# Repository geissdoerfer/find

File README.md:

# Efficient neighbor discovery and synchronization in battery-free wireless networks with FIND and FLYNC

This repository hosts the artifacts accompanying our NSDI 2021 paper, which introduces FIND and FLYNC.
FIND is the first neighbor discovery protocol for battery-free networks; it uses randomized waiting to minimize discovery latency in the face of intermittency.
FLYNC synchronizes indoor light harvesting devices to the powerline-induced brightness variations of state-of-the-art lamps; it further speeds up discovery when used in tandem with FIND.

In addition to the Python implementation of the analytical FIND model, we provide the hardware design of the prototype battery-free node and the source code of the firmware we used to evaluate FIND and FLYNC.

To get an overview, visit [our website](https://find.nes-lab.org).
For a detailed description and evaluation results, take a look at [our paper](https://nes-lab.org/pubs/2021-Geissdoerfer-Find.pdf).

## FIND Python Model

We provide a Python implementation of the analytical model of the FIND protocol, allowing to reproduce key results of our paper.
For a detailed description and examples, check out the [`/model`](./model/) directory.

## Hardware Design

We built a tiny, battery-free wireless node to evaluate FIND and FLYNC on real hardware.
The [`/hardware`](./hardware) directory contains the corresponding schematics and layout files.

## Firmware

The C code in the [`/firmware`](./firmware) directory implements the FIND protocol and the FLYNC synchronization mechanism on our prototype battery-free node.

## People

FIND and FLYNC are being developed at the Networked Embedded Systems Lab at TU Dresden.

The main contributors are:

 - [Kai Geissdoerfer](https://scholar.google.com/citations?user=k8YZfQEAAAAJ)
 - [Marco Zimmerling](https://wwwpub.zih.tu-dresden.de/~mzimmerl/)

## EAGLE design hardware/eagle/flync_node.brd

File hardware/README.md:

# FIND and FLYNC hardware

This directory contains the design files for a 29mm x 29mm battery-free wireless node.
The node is powered by three IXYS KXOB025-5X3F solar panels and buffers energy in a 47uF multi-layer ceramic capacitor.
It implements a circuit to extract a clock signal from variations of the solar panel current caused by powerline flicker of lamps.

Key specifications:
 - TI BQ25505 boost charger with maximum power point tracking
 - Nordic Semiconductor nRF52840 2.4GHz wireless MCU (BLE/802.15.4)
    - ARM Cortex-M4F 64MHz CPU with FPU
    - 1MB flash, 256kB S-RAM
 - 47uF capacitor in 0805 package

If you have questions or need help with manufacturing the hardware, get in touch with us!

## Pinout

We use a head-less 6-pin Tag-Connect header to break out 6 signals from the FLYNC node.

| Pin number | Signal   | Description                            |
|------------|----------|----------------------------------------|
| 1          | SWDIO    | ARM Serial Wire Debug I/O              |
| 2          | SWDCLK   | ARM Serial Wire Debug Clock            |
| 3          | PIN_DBG1 | nRF52 GPIO for debugging via e.g. UART |
| 4          | PIN_DBG2 | nRF52 GPIO for debugging via e.g. UART |
| 5          | VCC      | Output of BQ25504 and supply of nRF52  |
| 6          | GND      | Ground                                 |

Use a [Tag-Connect TC2030-IDC-NL cable](https://www.tag-connect.com/product/tc2030-idc-nl) cable to connect to this header:

## Development setup

We found the following setup convenient:

 - Lab bench power supply with 3.3V output
 - Breadboard and some jumper cables
 - [J-Link Mini Edu](https://www.segger.com/products/debug-probes/j-link/models/j-link-edu-mini/)
 - SPST push button
 - [Tag-Connect TC2030-IDC-NL cable](https://www.tag-connect.com/product/tc2030-idc-nl)

Connect the power supply GND to the breadboard GND rail and the power supply 3.3V to the breadboard power rail.
Connect GND (pin 6) of the cable to the GND rail on the breadboard and VCC (pin 5) of the cable to any unused row of the breadboard.
Connect the push button between this rail (with node VCC) and the breadboard 3.3V rail.
Connect the Vref of the J-Link to the 3.3V rail of the breadboard and the GND of the J-Link to the GND rail of the breadboard.
Finally, connect the SWDIO and SWDCLK pins of the J-Link to pins 1 and 2 of the cable.

By pushing the button, you can temporarily power the node from the 3.3V power supply to flash new code.
After releasing the push button, the node will continue to run from harvested energy.

For debugging, you can attach a logic analyzer or scope to pins 3 and 4 of the cable and an analog channel to the node's voltage rail (pin 5).
Keep in mind that there may be significant current flowing into these inputs, interfering with the node's operation.

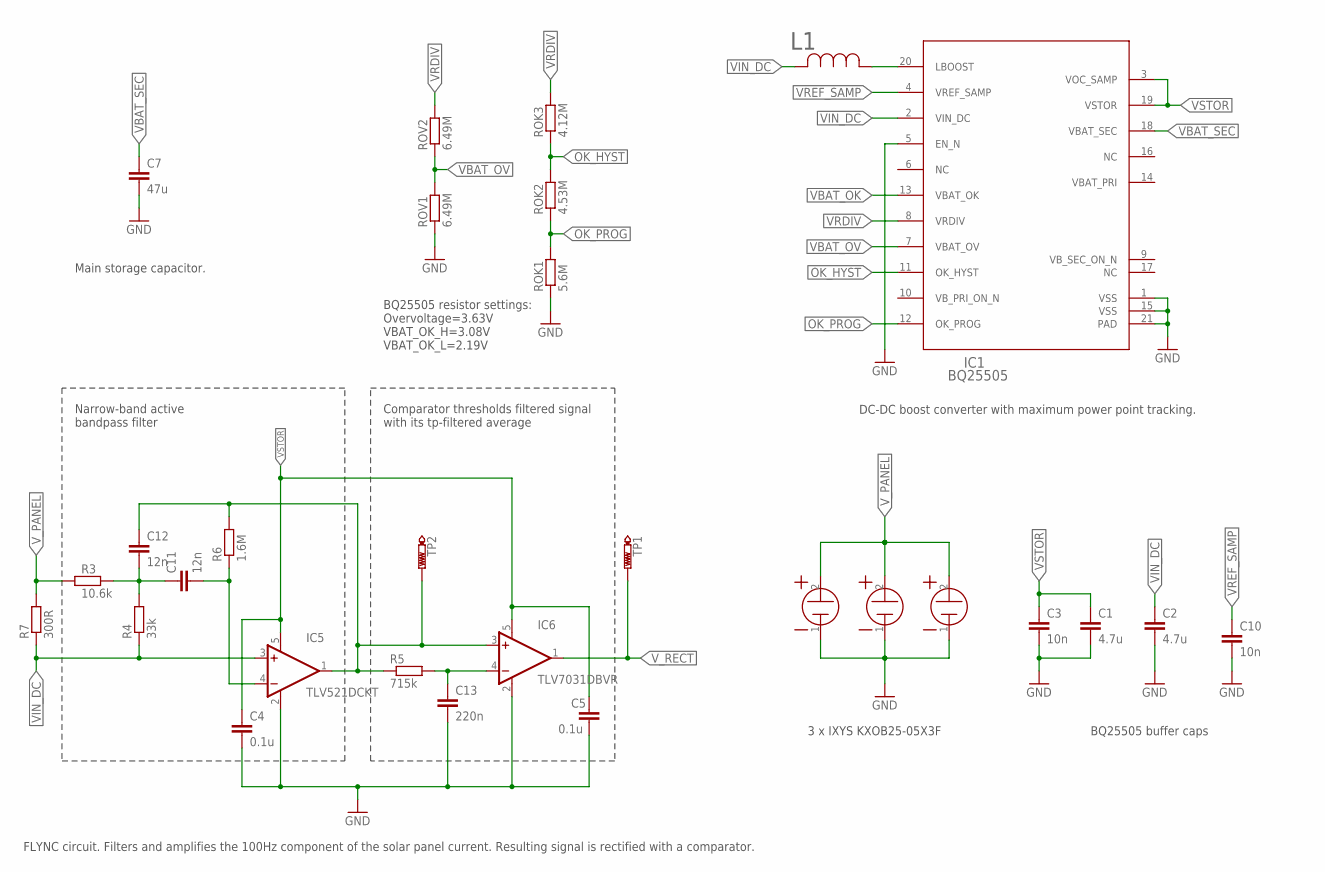
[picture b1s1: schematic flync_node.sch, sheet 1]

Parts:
C1, C2: 4.7u; CAPC1005X55
C3, C10: 10n; CAPC1005X55
C4, C5: 0.1u; CAPC1005X55
C7: 47u; CAPC2012X145
C11, C12: 12n; CAPC2012X145
C13: 220n; CAPC1005X55
H1, H2, H3: IXYSKXOB25-05X3F; IXYS23X8
IC1: BQ25505; RGR0020A
IC5: TLV521DCKT; DCK5
IC6: TLV7031DBVR; DBV5-L
L1: LBR2518T220KIND1007_47N_TAI-L; IND1007_47N_TAI-L
R3: 10.6k; RESC1005X40
R4: 33k; RESC1005X40
R5: 715k; RESC1005X40
R6: 1.6M; RESC1005X40
R7: 300R; RESC1608X55
ROK1: 5.6M; RESC1005X40
ROK2: 4.53M; RESC1005X40
ROK3: 4.12M; RESC1005X40
ROV1, ROV2: 6.49M; RESC1005X40
TP1, TP2: PTR1TP08R; TP08R

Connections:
GND: C1.2, C2.2, C3.2, C4.2, C5.2, C7.2, C10.2, C13.2, H1.1, H2.1, H3.1, IC1.1 (VSS), IC1.5 (EN_N), IC1.15 (VSS), IC1.21 (PAD), IC5.2 (V-), IC6.2 (V-), ROK1.1, ROV1.1; also elsewhere on the board
unnamed: IC1.20 (LBOOST), L1.1
unnamed: C11.1, C12.2, R3.2, R4.2
unnamed: C11.2, IC5.4 (-IN), R6.1
unnamed: C12.1, IC5.1 (OUT), IC6.3 (+IN), R5.1, R6.2, TP2.TP
unnamed: C13.1, IC6.4 (-IN), R5.2
OK_HYST: IC1.11 (OK_HYST), ROK2.2, ROK3.1
OK_PROG: IC1.12 (OK_PROG), ROK1.2, ROK2.1
VBAT_OK: IC1.13 (VBAT_OK); also elsewhere on the board
VBAT_OV: IC1.7 (VBAT_OV), ROV1.2, ROV2.1
VBAT_PRI: IC1.14 (VBAT_PRI)
VBAT_SEC: C7.1, IC1.18 (VBAT_SEC)
VB_SEC_ON_N: IC1.9 (VB_SEC_ON_N)
VIN_DC: C2.1, IC1.2 (VIN_DC), IC5.3 (+IN), L1.2, R4.1, R7.1
VRDIV: IC1.8 (VRDIV), ROK3.2, ROV2.2
VREF_SAMP: C10.1, IC1.4 (VREF_SAMP)
VSTOR: C1.1, C3.1, C4.1, C5.1, IC1.3 (VOC_SAMP), IC1.19 (VSTOR), IC5.5 (V+), IC6.5 (V+); also elsewhere on the board
V_PANEL: H1.2, H2.2, H3.2, R3.1, R7.2
V_RECT: IC6.1 (OUT), TP1.TP; also elsewhere on the board

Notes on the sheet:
FLYNC circuit. Filters and amplifies the 100Hz component of the solar panel current. Resulting signal is rectified with a comparator.
Narrow-band active bandpass filter
Comparator thresholds filtered signal with its tp-filtered average
DC-DC boost converter with maximum power point tracking.
BQ25505 resistor settings: Overvoltage=3.63V VBAT_OK_H=3.08V VBAT_OK_L=2.19V
Main storage capacitor.
BQ25505 buffer caps
3 x IXYS KXOB25-05X3F

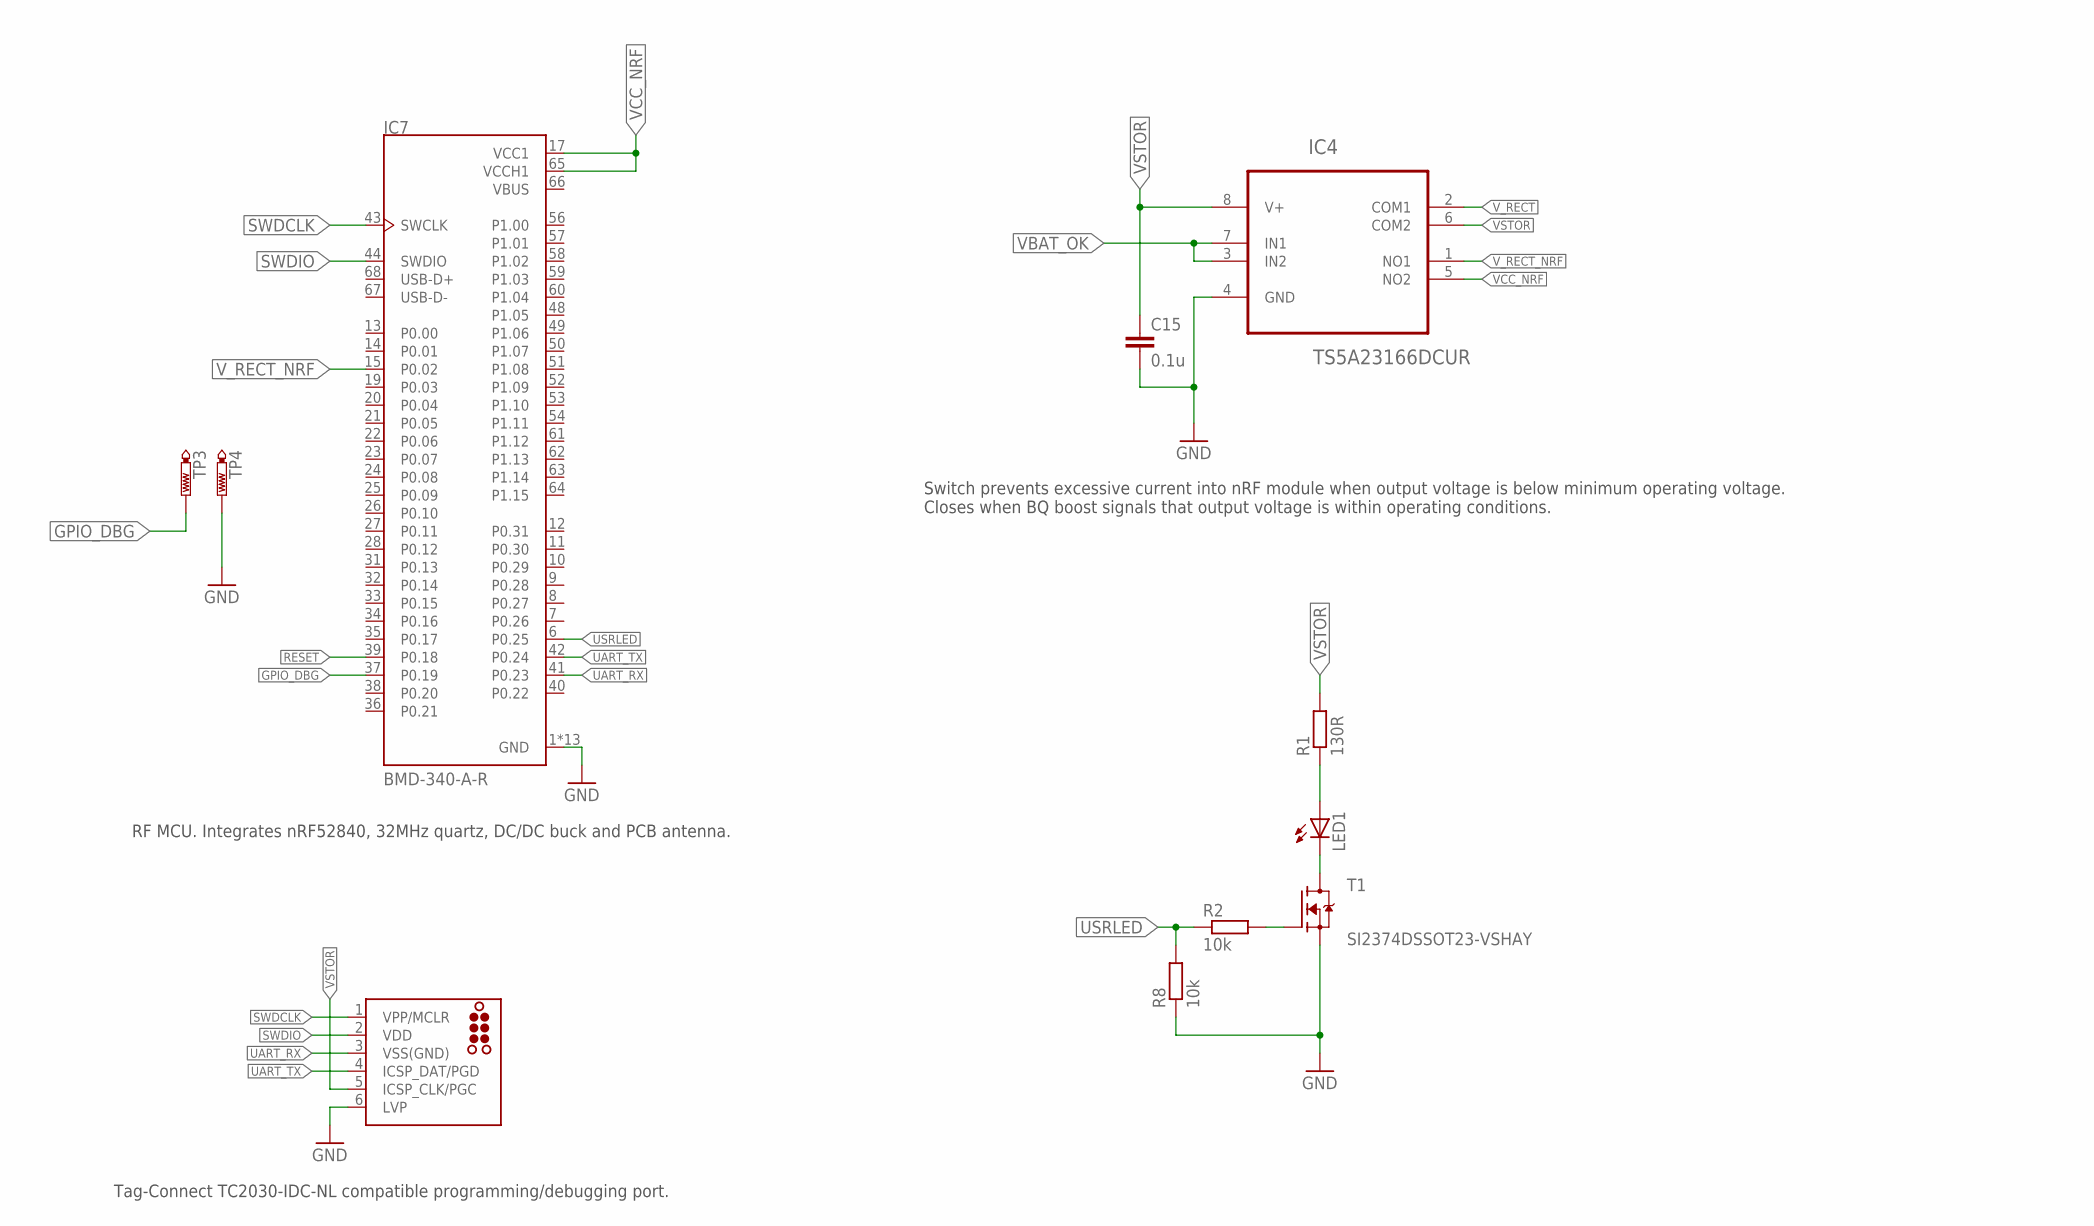
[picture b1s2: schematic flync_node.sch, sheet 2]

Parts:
C15: 0.1u; CAPC1005X55
IC4: TS5A23166DCUR; SOP50P310X90-8N
IC7: BMD-340-A-R; RIGADO_BMD-340-A-R
J1: TC2030-MCP-NL
LED1: 598-8130-107FLED_0805; LEDC2012X75
R1: 130R; RESC1608X55
R2, R8: 10k; RESC1005X40
T1: SI2374DSSOT23-VSHAY; SOT95P237X112-3
TP3, TP4: PTR1TP16SQ; TP16SQ

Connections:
GND: C15.2, IC4.4 (GND), IC7.1 (GND), IC7.2 (GND), IC7.3 (GND), IC7.4 (GND), IC7.5 (GND), IC7.16 (GND), IC7.18 (GND), IC7.29 (GND), IC7.30 (GND), IC7.45 (GND), IC7.46 (GND), IC7.47 (GND), IC7.55 (GND), J1.6 (LVP), R8.1, T1.2 (S), TP4.TP; also elsewhere on the board
GPIO_DBG: IC7.37 (P0.19), TP3.TP
unnamed: LED1.2 (A), R1.1
unnamed: LED1.1 (C), T1.3 (D)
unnamed: R2.2, T1.1 (G)
RESET: IC7.39 (P0.18)
SWDCLK: IC7.43 (SWCLK), J1.1 (VPP/MCLR)
SWDIO: IC7.44 (SWDIO), J1.2 (VDD)
UART_RX: IC7.41 (P0.23), J1.3 (VSS(GND))
UART_TX: IC7.42 (P0.24), J1.4 (ICSP_DAT/PGD)
USRLED: IC7.6 (P0.25), R2.1, R8.2
VBAT_OK: IC4.3 (IN2), IC4.7 (IN1); also elsewhere on the board
VBUS: IC7.66 (VBUS)
VCC_NRF: IC4.5 (NO2), IC7.17 (VCC1), IC7.65 (VCCH1)
VSTOR: C15.1, IC4.6 (COM2), IC4.8 (V+), J1.5 (ICSP_CLK/PGC), R1.2; also elsewhere on the board
V_RECT: IC4.2 (COM1); also elsewhere on the board
V_RECT_NRF: IC4.1 (NO1), IC7.15 (P0.02)

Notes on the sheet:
Switch prevents excessive current into nRF module when output voltage is below minimum operating voltage. Closes when BQ boost signals that output voltage is within operating conditions.
RF MCU. Integrates nRF52840, 32MHz quartz, DC/DC buck and PCB antenna.
Tag-Connect TC2030-IDC-NL compatible programming/debugging port.

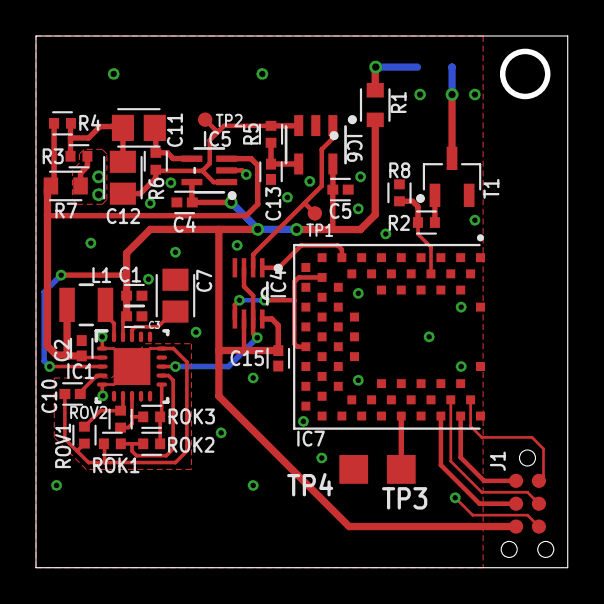
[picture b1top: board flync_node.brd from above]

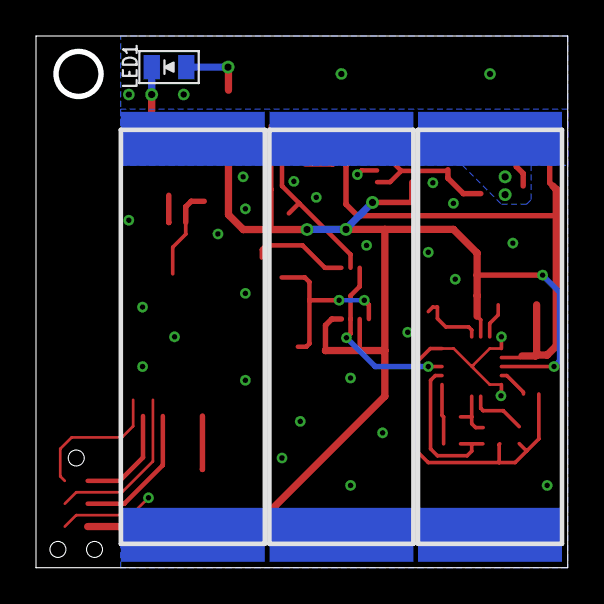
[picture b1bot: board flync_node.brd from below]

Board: 2 copper layers, 29.2 x 29.2 mm, 40 parts (4 on the bottom side), 28 nets.

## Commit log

2021-02-18 added hardware design files
2021-02-24 added python package
2021-02-24 travis: run tests with tox
2021-02-24 travis: added tox.ini file
2021-02-24 travis: added setuptools dependency
2021-02-24 dismissed tox
2021-02-24 travis: fix install dependencies
2021-02-24 hardware: added schematic and layout as pdf
2021-02-24 added fimware
2021-02-24 travis: fix install path
2021-02-24 model: bumpversion v0.0.1 --> v0.0.2
2021-02-24 moved firmware readme to correct dir
2021-02-25 hardware: added readme
2021-02-25 hardware: prettier pics in readme
2021-02-25 model: fixed missing pathlib dependency
2021-02-25 model: added examples for reproducing paper results
2021-02-25 extended readmes
2021-02-25 model: renamed 'shape' to 'scale'
2021-03-01 revised top level readme
2021-03-01 model: simplified activity/cdf example plot
2021-03-01 model: renamed 'shape' to 'scale' in example and distributions module
2021-03-01 model: revised readme
2021-03-01 model: made matplotlib an extra dependency
2021-03-01 model: added a few comments
2021-03-01 bumpversion v0.0.3 --> v0.0.4
2021-03-01 more README work
2021-03-02 model: fixed typo in Readme
2021-03-02 revised readmes
2021-03-03 WIP: add instructions for reproducing plots on HPC cluster
2021-03-03 model: more scripts for reproducing paper results
2021-07-16 firmware: make sure _build exists
2021-09-28 firmware: fixed minor bugs in inverse transform sampling
2021-09-28 firmware: clean jump from executing from flash to executing from RAM
2021-12-09 hardware: added link to BOM

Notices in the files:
parts and their libraries:
flicker-sync: ©2009 ROFA.cz - modified and updated by Robert Darlington ‹rdarlington@gmail.com›
COPYRIGHT: Copyright (C) 2018 Accelerated Designs. All rights reserved
